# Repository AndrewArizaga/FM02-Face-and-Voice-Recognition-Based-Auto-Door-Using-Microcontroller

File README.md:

# FM02: Face and Voice Recognition Based Auto Door Using Microcontroller

## Overview
The **Face and Voice Recognition Based Auto Door** project is a cutting-edge solution to automate door access using advanced face and voice recognition technologies. By integrating the ESP32 CAM module and a serial voice recognition module with an Arduino Uno microcontroller, this project ensures secure, efficient, and selective access control, overcoming the limitations of traditional motion-based systems.

---

## Key Objectives
- **Dual Authentication:** Combine face and voice recognition for enhanced security.
- **Selective Access:** Restrict access to only authorized individuals.
- **Hands-Free Automation:** Provide convenient, hands-free access, especially for the elderly or disabled.

---

## Hardware Components
- **ESP32 CAM Module:** Captures and recognizes facial features in real-time.
- **Arduino Uno:** Acts as the central controller, coordinating hardware operations.
- **Serial Voice Recognition Module & Microphone:** Captures and verifies spoken commands for voice authentication.
- **Stepper Motor & Driver:** Controls the automated door mechanism.
- **Power Supply:** Provides 5V for logic circuits and 12V for the stepper motor.

---

## System Workflow
1. **Face Recognition:**  
   The ESP32 CAM captures and validates the user's face against a stored database of authorized profiles.
2. **Voice Command:**  
   The microphone captures the user's voice command, which is verified by the serial voice recognition module.
3. **Door Control:**  
   Upon successful dual-layer authentication, the Arduino Uno triggers the stepper motor to open the door. The door closes automatically after a timeout or upon receiving a "close" command.

---

## Project Focus
This project emphasizes:
- **Practical Implementation:** Integration of face and voice recognition technologies with embedded systems.
- **Efficiency:** Ensuring seamless and reliable operation with minimal errors.
- **Security:** Providing robust access control to protect against unauthorized use.

---

## Future Applications
- **Smart Home Integration:** Automate home entry with advanced security measures.
- **Workplace Automation:** Enhance security for restricted access areas.
- **IoT Ecosystem:** Enable real-time remote control and monitoring through IoT connectivity.

---

## How to Use
1. Approach the door; the system will initiate **face recognition**.
2. Speak the predefined **voice command** for authentication.
3. If both steps are successful, the door will open automatically.

---

Feel free to let me know if further enhancements are needed or if you'd like to add an additional section!

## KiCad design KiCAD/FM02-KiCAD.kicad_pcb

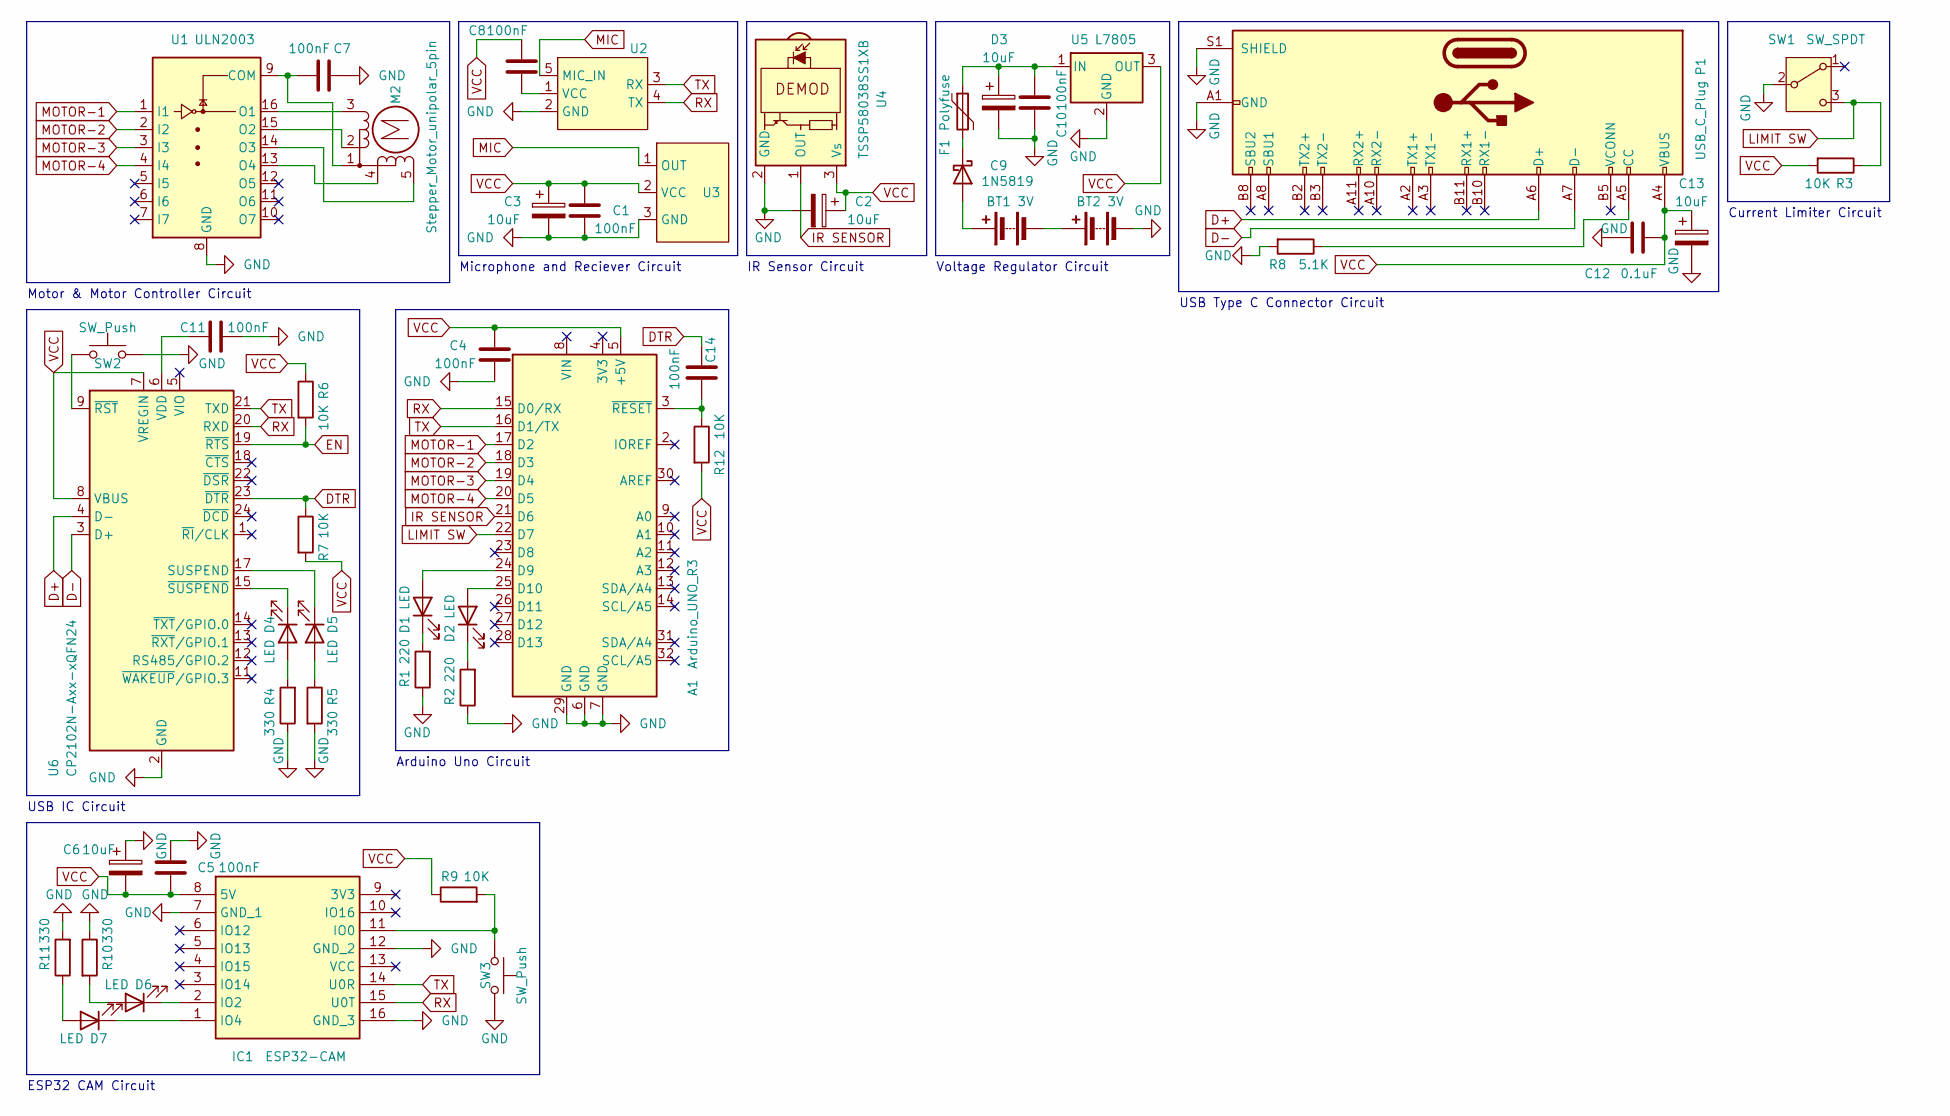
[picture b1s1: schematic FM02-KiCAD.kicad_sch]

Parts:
A1: Arduino_UNO_R3
BT1, BT2: 3V; BatteryHolder_Keystone_2462_2xAA
C1, C4, C5, C7, C8, C10, C11, C14: 100nF; C_0805_2012Metric_Pad1.18x1.45mm_HandSolder
C2, C3, C6, C9, C13: 10uF; C_0805_2012Metric_Pad1.18x1.45mm_HandSolder
C12: 0.1uF; C_0603_1608Metric_Pad1.08x0.95mm_HandSolder
D1, D2, D4, D5, D6, D7: LED; LED_0805_2012Metric_Pad1.15x1.40mm_HandSolder
D3: 1N5819; D_DO-41_SOD81_P10.16mm_Horizontal
F1: Polyfuse; Fuse_1206_3216Metric_Pad1.42x1.75mm_HandSolder
IC1: ESP32-CAM; ESP32CAM; Manufacturer_Part_Number ESP32-CAM
M2: Stepper_Motor_unipolar_5pin; PinHeader_1x05_P2.54mm_Vertical
P1: USB_C_Plug; USB_C_Receptacle_HRO_TYPE-C-31-M-12
R1, R2: 220; R_0805_2012Metric_Pad1.20x1.40mm_HandSolder
R3, R6, R7, R9, R12: 10K; R_0805_2012Metric_Pad1.20x1.40mm_HandSolder
R4, R5, R10, R11: 330; R_0805_2012Metric_Pad1.20x1.40mm_HandSolder
R8: 5.1K; R_0805_2012Metric_Pad1.20x1.40mm_HandSolder
SW1: SW_SPDT; SW_Slide_SPDT_Straight_CK_OS102011MS2Q
SW2, SW3: SW_Push; SW_PUSH_6mm
U1: ULN2003; DIP-16_W7.62mm_Socket_LongPads
U2: PinHeader_1x05_P2.54mm_Vertical
U3: PinHeader_1x03_P2.54mm_Vertical
U4: TSSP58038SS1XB; Vishay_MINICAST-3Pin
U5: L7805; TO-220-3_Vertical
U6: CP2102N-Axx-xQFN24; QFN-24-1EP_4x4mm_P0.5mm_EP2.6x2.6mm

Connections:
D+: P1.A6 (D+), U6.4 (D-)
D-: P1.A7 (D-), U6.3 (D+)
DTR: C14.1, R7.1, U6.23 (~DTR)
EN: R6.2, U6.19 (~RTS)
GND: A1.6 (GND), A1.7 (GND), A1.29 (GND), BT2.2 (-), C1.2, C2.2, C3.2, C4.1, C5.2, C6.1, C7.1, C9.2, C10.2, C11.2, C12.2, C13.2, IC1.7 (GND_1), IC1.12 (GND_2), IC1.16 (GND_3), P1.A1 (GND), P1.A12 (GND), P1.B1 (GND), P1.B12 (GND), P1.S1 (SHIELD), R1.1, R2.1, R4.1, R5.2, R8.2, R10.1, R11.2, SW1.2 (B), SW2.2, SW3.2, U1.8 (GND), U2.2 (GND), U3.3 (GND), U4.2 (GND), U5.2 (GND), U6.2 (GND), U6.25 (GND)
IR SENSOR: A1.21 (D6), U4.1 (OUT)
LIMIT SW: A1.22 (D7), R3.1, SW1.3 (C)
MIC: U2.5 (MIC_IN), U3.1 (OUT)
MOTOR-1: A1.17 (D2), U1.1 (I1)
MOTOR-2: A1.18 (D3), U1.2 (I2)
MOTOR-3: A1.19 (D4), U1.3 (I3)
MOTOR-4: A1.20 (D5), U1.4 (I4)
unnamed: A1.24 (D9), D1.2 (A)
unnamed: A1.25 (D10), D2.2 (A)
unnamed: A1.3 (~RESET), C14.2, R12.1
unnamed: BT1.1 (+), D3.2 (A)
unnamed: BT1.2 (-), BT2.1 (+)
unnamed: D1.1 (K), R1.2
unnamed: D2.1 (K), R2.2
unnamed: D3.1 (K), F1.2
unnamed: D4.2 (A), R4.2
unnamed: D4.1 (K), U6.15 (~SUSPEND)
unnamed: D5.2 (A), R5.1
unnamed: D5.1 (K), U6.17 (SUSPEND)
unnamed: D6.2 (A), R10.2
unnamed: D6.1 (K), IC1.2 (IO2)
unnamed: D7.2 (A), R11.1
unnamed: D7.1 (K), IC1.1 (IO4)
unnamed: IC1.11 (IO0), R9.2, SW3.1
unnamed: M2.3 (-), U1.16 (O1)
unnamed: P1.A5 (CC), R8.1
unnamed: C7.2, M2.1, U1.9 (COM)
unnamed: M2.2, U1.15 (O2)
unnamed: M2.5, U1.14 (O3)
unnamed: M2.4, U1.13 (O4)
unnamed: C8.2, U2.1 (VCC)
unnamed: C9.1, C10.1, F1.1, U5.1 (IN)
unnamed: C11.1, U6.6 (VDD)
unnamed: SW2.1, U6.9 (~RST)
RX: A1.15 (D0/RX), IC1.15 (U0T), U2.4 (TX), U6.20 (RXD)
TX: A1.16 (D1/TX), IC1.14 (U0R), U2.3 (RX), U6.21 (TXD)
VCC: A1.5 (+5V), C1.1, C2.1, C3.1, C4.2, C5.1, C6.2, C8.1, C12.1, C13.1, IC1.8 (5V), P1.A4 (VBUS), P1.A9 (VBUS), P1.B4 (VBUS), P1.B9 (VBUS), R3.2, R6.1, R7.2, R9.1, R12.2, U3.2 (VCC), U4.3 (Vs), U5.3 (OUT), U6.7 (VREGIN), U6.8 (VBUS)

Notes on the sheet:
Current Limiter Circuit
Arduino Uno Circuit
USB IC Circuit
Microphone and Reciever Circuit
Voltage Regulator Circuit
Motor & Motor Controller Circuit
ESP32 CAM Circuit
IR Sensor Circuit
USB Type C Connector Circuit

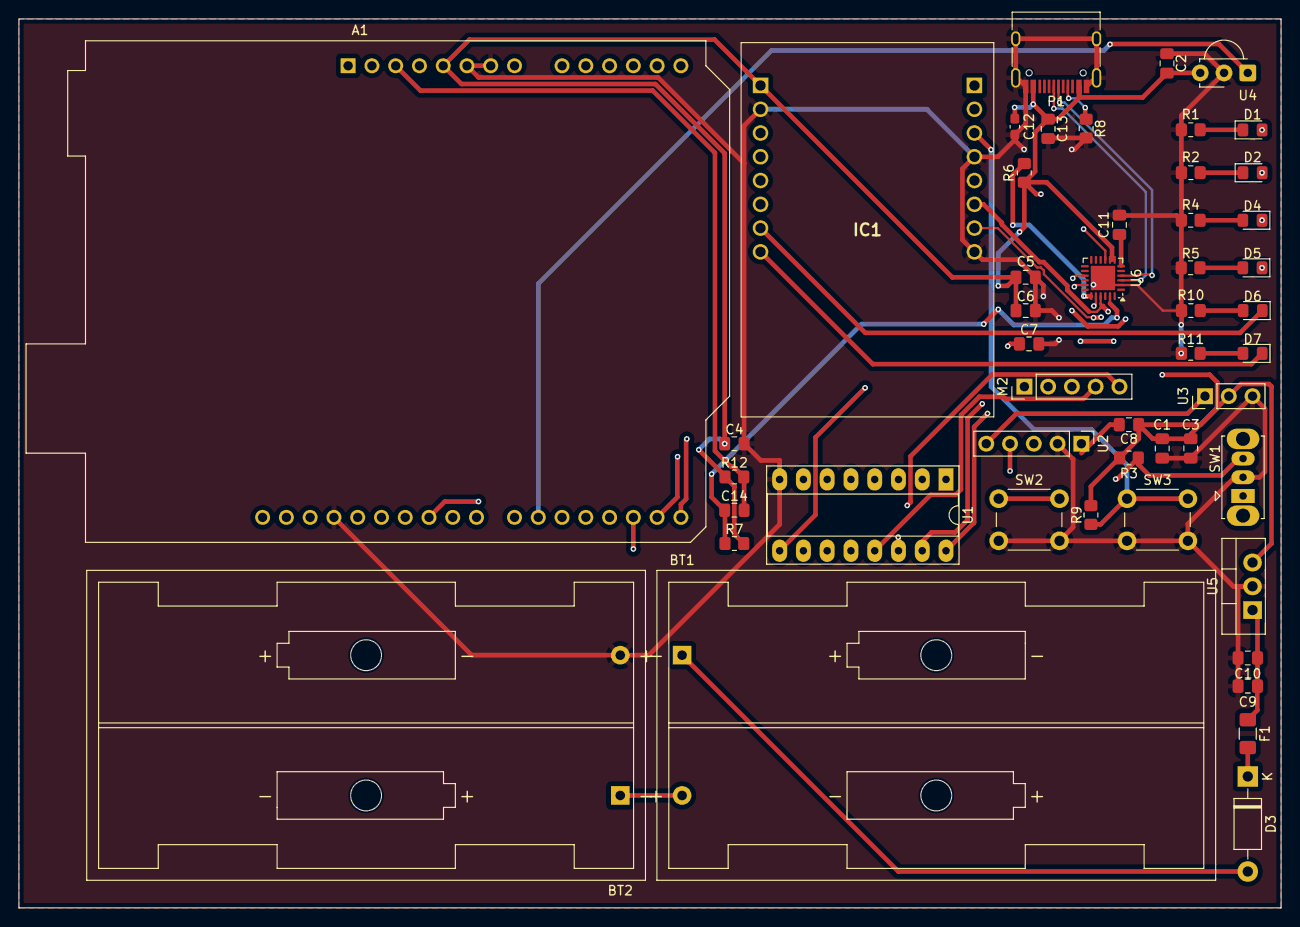
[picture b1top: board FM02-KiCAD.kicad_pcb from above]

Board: 4 copper layers, 134.9 x 95.0 mm, 49 parts (0 on the bottom side), 42 nets.

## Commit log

2024-12-27 Version 1
2024-12-27 Rename Audio Module.bak to KiCAD/Audio Module.bak
2024-12-27 Rename Audio Module.kicad_sym to KiCAD/Audio Module.kicad_sym
2024-12-27 Rename FM02-KiCAD.kicad_pcb to KiCAD/FM02-KiCAD.kicad_pcb
2024-12-27 Rename FM02-KiCAD.kicad_prl to KiCAD/FM02-KiCAD.kicad_prl
2024-12-27 Rename FM02-KiCAD.kicad_pro to KiCAD/FM02-KiCAD.kicad_pro
2024-12-27 Rename FM02-KiCAD.kicad_sch to KiCAD/FM02-KiCAD.kicad_sch
2024-12-27 Rename fp-info-cache to KiCAD/fp-info-cache
2024-12-27 Rename fp-lib-table to KiCAD/fp-lib-table
2024-12-27 Rename sym-lib-table to KiCAD/sym-lib-table
2024-12-28 Rename FM02-KiCAD.pdf to PDFs&Images/FM02-KiCAD-Schematic-Ver-1.pdf
